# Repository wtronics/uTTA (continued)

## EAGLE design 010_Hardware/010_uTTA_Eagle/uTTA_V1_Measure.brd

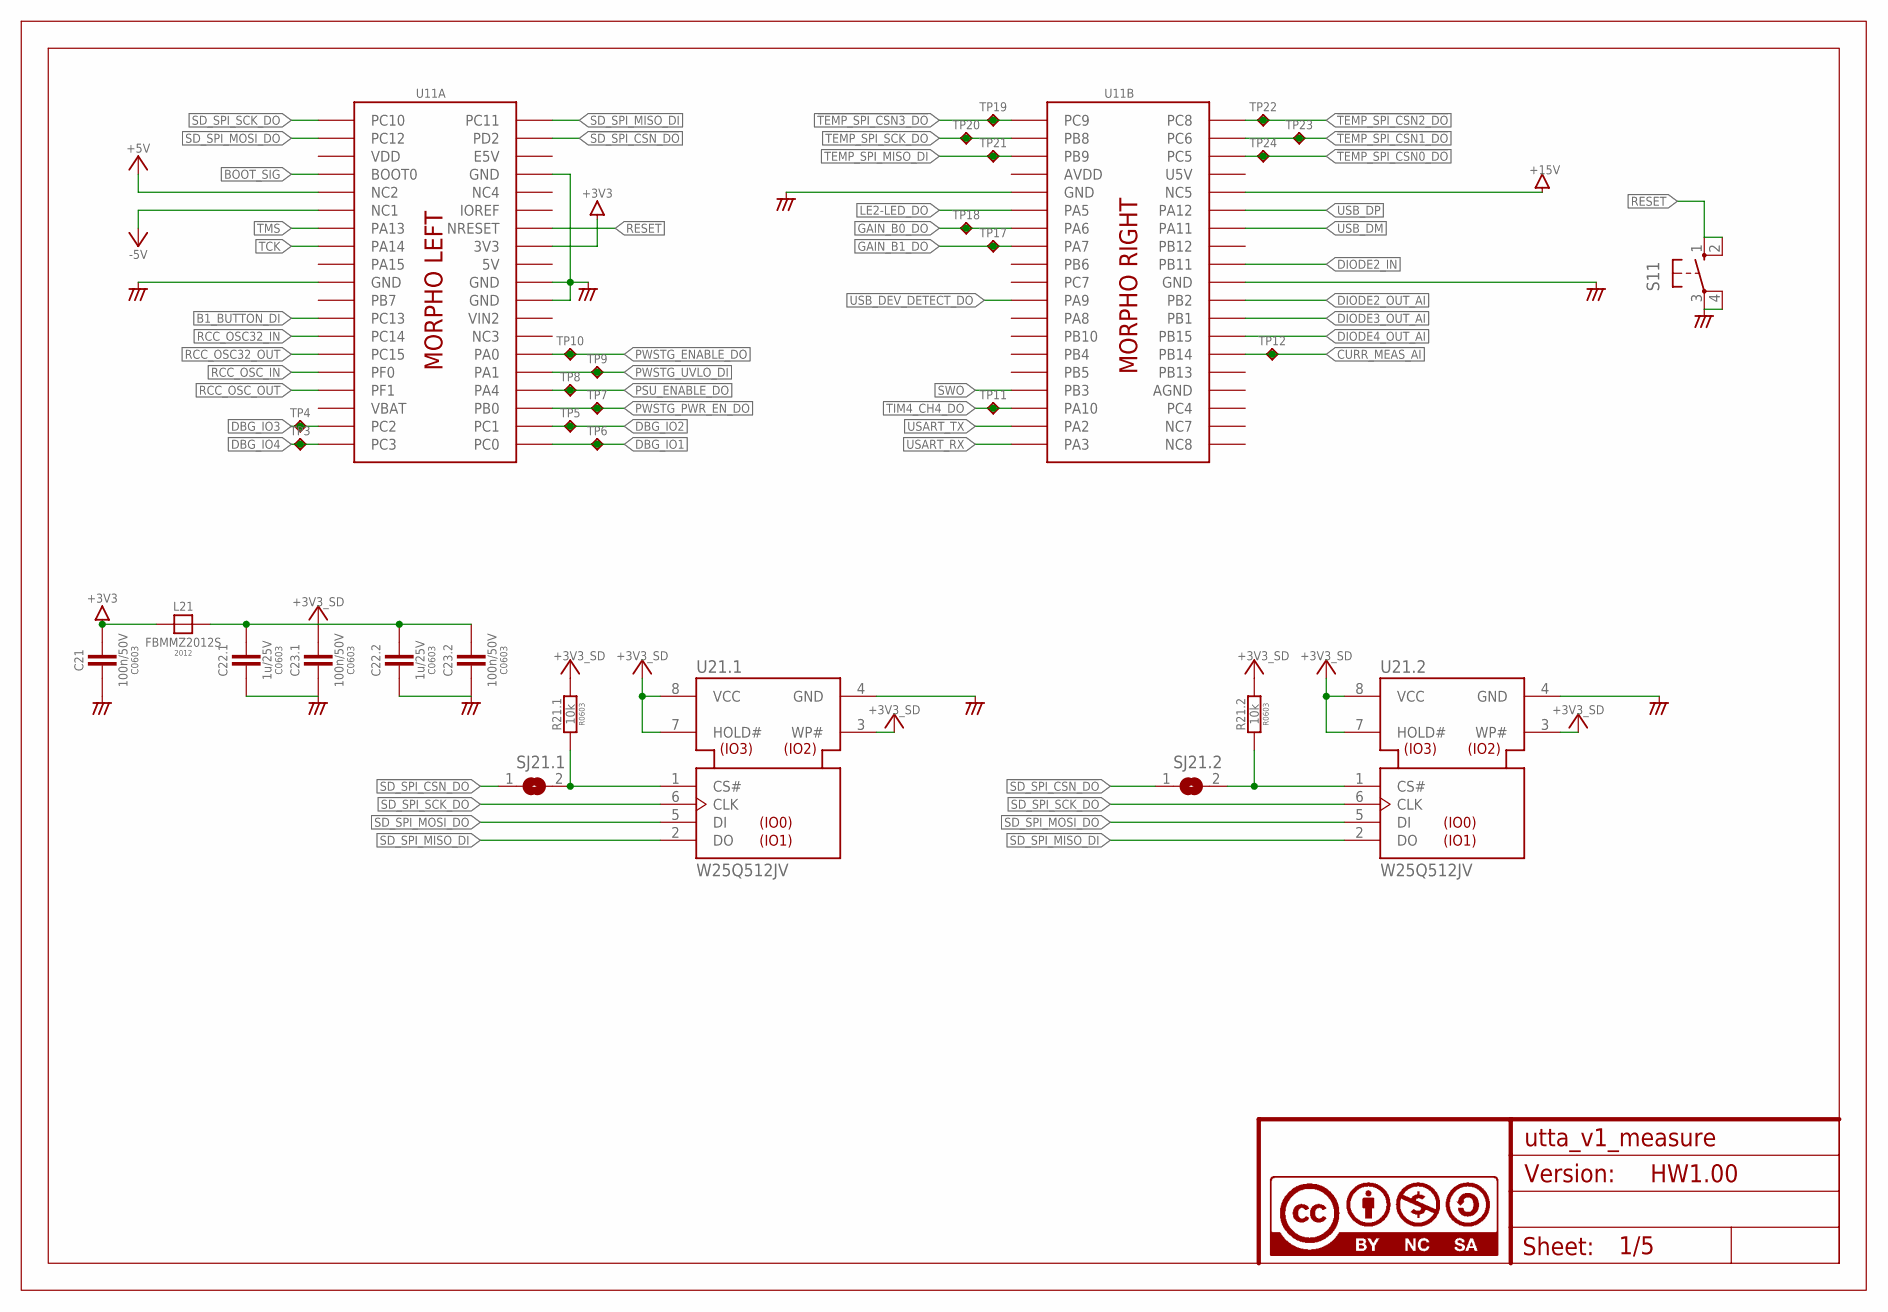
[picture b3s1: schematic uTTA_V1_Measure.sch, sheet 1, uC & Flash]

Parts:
C21, C23.1, C23.2: 100n/50V; C0603
C22.1, C22.2: 1u/25V; C0603
L21: FBMMZ2012S; FB2012
R21.1, R21.2: 10k; R0603
S11: 10-XX; B3F-10XX
SJ21.1, SJ21.2: SJ
TP3, TP4, TP5, TP6, TP7, TP8, TP9, TP10, TP11, TP12, TP17, TP18, TP19, TP20, TP21, TP22, TP23, TP24: TPC90H30; C90H30
U11: NUCLEO_F103_BOT; NUCLEO_BRD64_LOWER
U21.1, U21.2: W25Q512JV; SO08W
U$3: A4L-LOC_CC_BY_NC_SA; A4_LOC_CC_BY_NC_SA

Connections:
5V: U11.L_5V (5V)
!SD_SPI_CSN_DO: SJ21.1.1, SJ21.2.1, U11.L_PD2 (PD2)
!TEMP_SPI_CSN0_DO: TP24.P$1, U11.R_PC5 (PC5); also elsewhere on the board
!TEMP_SPI_CSN1_DO: TP23.P$1, U11.R_PC6 (PC6); also elsewhere on the board
!TEMP_SPI_CSN2_DO: TP22.P$1, U11.R_PC8 (PC8); also elsewhere on the board
!TEMP_SPI_CSN3_DO: TP19.P$1, U11.R_PC9 (PC9); also elsewhere on the board
+3V3: C21.1, L21.1, U11.L_3V3 (3V3); also elsewhere on the board
+5V: U11.L_NC2 (NC2); also elsewhere on the board
+5V/4: C22.1.1, C22.2.1, C23.1.1, C23.2.1, L21.2, R21.1.1, R21.2.1, U21.1.3 (WP#), U21.1.7 (HOLD#), U21.1.8 (VCC), U21.2.3 (WP#), U21.2.7 (HOLD#), U21.2.8 (VCC)
+15V: U11.R_NC5 (NC5)
-5V: U11.L_NC1 (NC1); also elsewhere on the board
AGND: C21.2, C22.1.2, C22.2.2, C23.1.2, C23.2.2, S11.3, S11.4 (P1), U11.L_GND (GND), U11.L_GND3 (GND), U11.L_GND4 (GND), U11.L_GND5 (GND), U11.R_AGND (AGND), U11.R_GND7 (GND), U11.R_GND8 (GND), U21.1.4 (GND), U21.2.4 (GND); also elsewhere on the board
AVDD: U11.R_AVDD (AVDD)
B1_BUTTON_DI: U11.L_PC13 (PC13)
BOOT_SIG: U11.L_BOOT0 (BOOT0)
CURR_MEAS_AI: TP12.P$1, U11.R_PB14 (PB14)
DBG_IO1: TP6.P$1, U11.L_PC0 (PC0)
DBG_IO2: TP5.P$1, U11.L_PC1 (PC1)
DBG_IO3: TP4.P$1, U11.L_PC2 (PC2)
DBG_IO4: TP3.P$1, U11.L_PC3 (PC3)
DIODE2_IN: U11.R_PB11 (PB11); also elsewhere on the board
DIODE2_OUT_AI: U11.R_PB2 (PB2); also elsewhere on the board
DIODE3_OUT_AI: U11.R_PB1 (PB1); also elsewhere on the board
DIODE4_OUT_AI: U11.R_PB15 (PB15); also elsewhere on the board
E5V: U11.L_E5V (E5V)
GAIN_B0_DO: TP18.P$1, U11.R_PA6 (PA6); also elsewhere on the board
GAIN_B1_DO: TP17.P$1, U11.R_PA7 (PA7); also elsewhere on the board
LE2-LED_DO: U11.R_PA5 (PA5)
unnamed: R21.1.2, SJ21.1.2, U21.1.1 (CS#)
unnamed: R21.2.2, SJ21.2.2, U21.2.1 (CS#)
PSU_ENABLE_DO: TP8.P$1, U11.L_PA4 (PA4)
PWSTG_ENABLE_DO: TP10.P$1, U11.L_PA0 (PA0)
PWSTG_PWR_EN_DO: TP7.P$1, U11.L_PB0 (PB0)
PWSTG_UVLO_DI: TP9.P$1, U11.L_PA1 (PA1)
RCC_OSC32_IN: U11.L_PC14 (PC14)
RCC_OSC32_OUT: U11.L_PC15 (PC15)
RCC_OSC_IN: U11.L_PF0 (PF0)
RCC_OSC_OUT: U11.L_PF1 (PF1)
RESET: S11.1 (S), S11.2 (S1), U11.L_RESET (NRESET)
SD_SPI_MISO_DI: U11.L_PC11 (PC11), U21.1.2 (DO), U21.2.2 (DO)
SD_SPI_MOSI_DO: U11.L_PC12 (PC12), U21.1.5 (DI), U21.2.5 (DI); also elsewhere on the board
SD_SPI_SCK_DO: U11.L_PC10 (PC10), U21.1.6 (CLK), U21.2.6 (CLK); also elsewhere on the board
SWO: U11.R_PB3 (PB3)
TCK: U11.L_PA14 (PA14)
TEMP_SPI_MISO_DI: TP21.P$1, U11.R_PB9 (PB9); also elsewhere on the board
TEMP_SPI_SCK_DO: TP20.P$1, U11.R_PB8 (PB8); also elsewhere on the board
TIM4_CH4_DO: TP11.P$1, U11.R_PA10 (PA10)
TMS: U11.L_PA13 (PA13)
U5V: U11.R_U5V (U5V)
USART_RX: U11.R_PA3 (PA3)
USART_TX: U11.R_PA2 (PA2)
USB_DEV_DETECT_DO: U11.R_PA9 (PA9)
USB_DM: U11.R_PA11 (PA11)
USB_DP: U11.R_PA12 (PA12)
VBAT: U11.L_VBAT (VBAT)
VDD: U11.L_VDD (VDD)
VIN2: U11.L_VIN (VIN2)

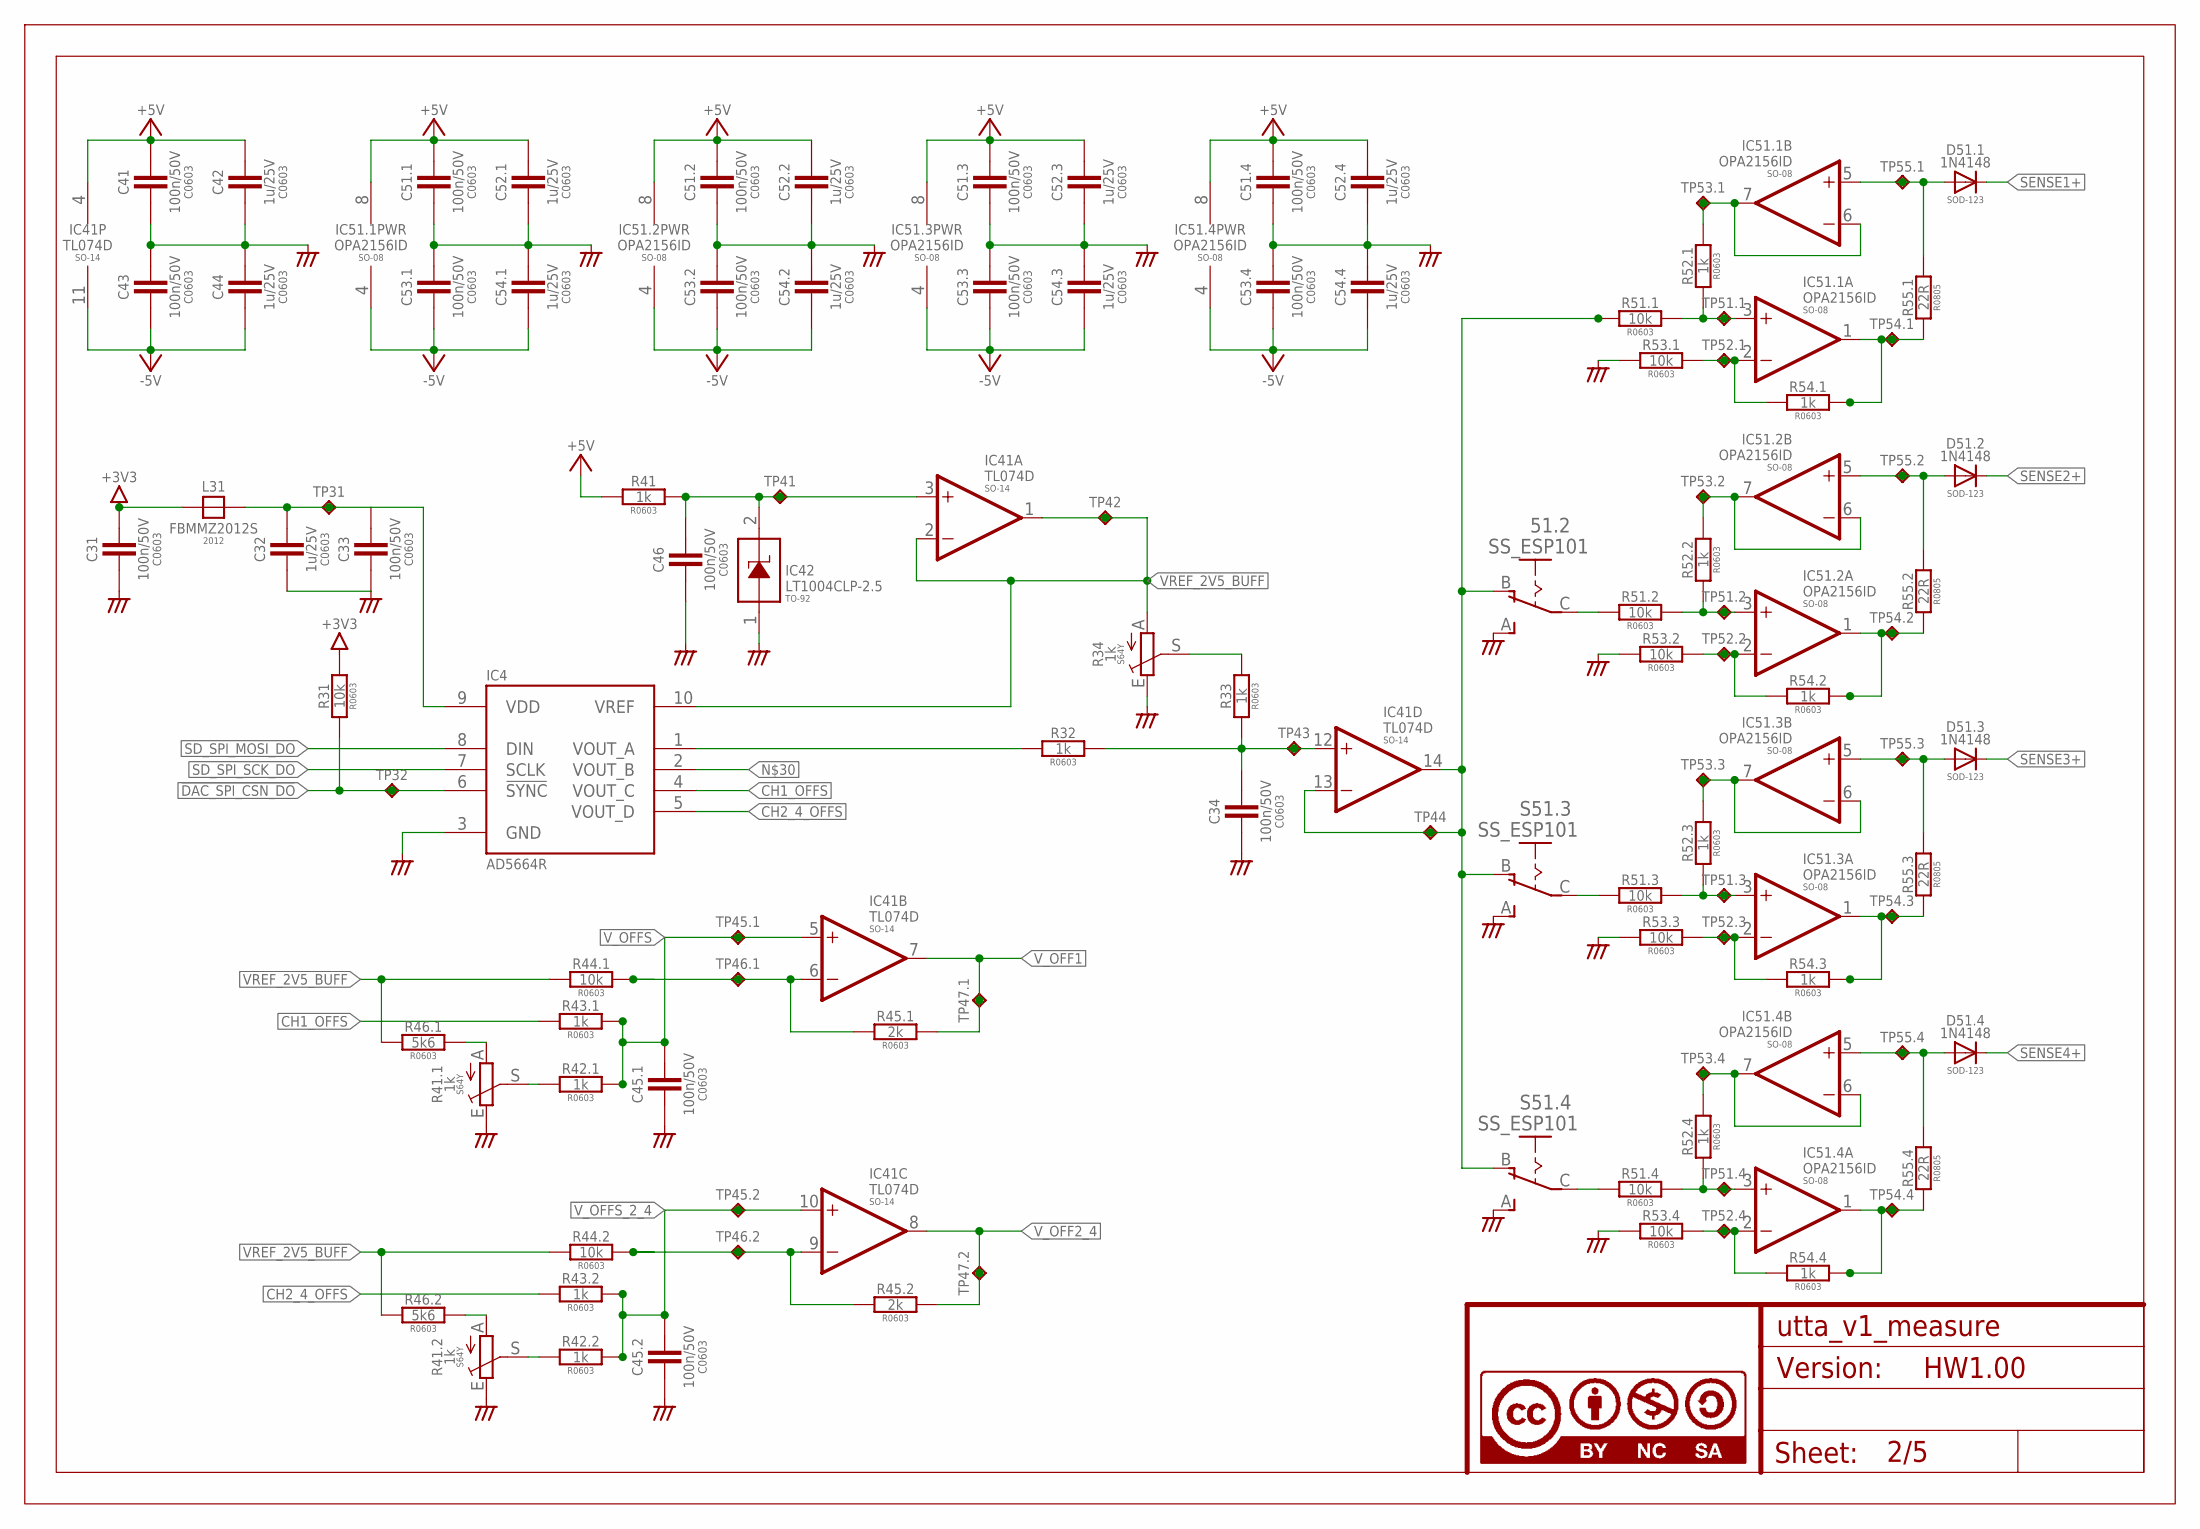
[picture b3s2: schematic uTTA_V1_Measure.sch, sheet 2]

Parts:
51.2: SS_ESP101
C31, C33, C34, C41, C43, C45.1, C45.2, C46, C51.1, C51.2, C51.3, C51.4, C53.1, C53.2, C53.3, C53.4: 100n/50V; C0603
C32, C42, C44, C52.1, C52.2, C52.3, C52.4, C54.1, C54.2, C54.3, C54.4: 1u/25V; C0603
D51.1, D51.2, D51.3, D51.4: 1N4148; SOD123
IC4: AD5664R; MSOP10
IC41: TL074D; SO14
IC42: LT1004CLP-2.5; TO92-
IC51.1, IC51.2, IC51.3, IC51.4: OPA2156ID; SO08
L31: FBMMZ2012S; FB2012
R31, R44.1, R44.2, R51.1, R51.2, R51.3, R51.4, R53.1, R53.2, R53.3, R53.4: 10k; R0603
R32, R33, R41, R42.1, R42.2, R43.1, R43.2, R52.1, R52.2, R52.3, R52.4, R54.1, R54.2, R54.3, R54.4: 1k; R0603
R34, R41.1, R41.2: 1k; S64Y
R45.1, R45.2: 2k; R0603
R46.1, R46.2: 5k6; R0603
R55.1, R55.2, R55.3, R55.4: 22R; R0805
S51.3, S51.4: SS_ESP101
TP31, TP32, TP41, TP42, TP43, TP44, TP45.1, TP45.2, TP46.1, TP46.2, TP47.1, TP47.2, TP51.1, TP51.2, TP51.3, TP51.4, TP52.1, TP52.2, TP52.3, TP52.4, TP53.1, TP53.2, TP53.3, TP53.4, TP54.1, TP54.2, TP54.3, TP54.4, TP55.1, TP55.2, TP55.3, TP55.4: TP; C90
U$10: A4L-LOC_CC_BY_NC_SA; A4_LOC_CC_BY_NC_SA

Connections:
!DAC_SPI_CSN_DO: IC4.6 (!SYNC), R31.2, TP32.P$1
+3V3: C31.1, L31.1, R31.1; also elsewhere on the board
+5V: C41.1, C42.1, C51.1.1, C51.2.1, C51.3.1, C51.4.1, C52.1.1, C52.2.1, C52.3.1, C52.4.1, IC41.4 (V+), IC51.1.8 (V+), IC51.2.8 (V+), IC51.3.8 (V+), IC51.4.8 (V+), R41.1; also elsewhere on the board
-5V: C43.2, C44.2, C53.1.2, C53.2.2, C53.3.2, C53.4.2, C54.1.2, C54.2.2, C54.3.2, C54.4.2, IC41.11 (V-), IC51.1.4 (V-), IC51.2.4 (V-), IC51.3.4 (V-), IC51.4.4 (V-); also elsewhere on the board
AGND: 51.2.A (S), C31.2, C32.2, C33.2, C34.2, C41.2, C42.2, C43.1, C44.1, C45.1.2, C45.2.2, C46.2, C51.1.2, C51.2.2, C51.3.2, C51.4.2, C52.1.2, C52.2.2, C52.3.2, C52.4.2, C53.1.1, C53.2.1, C53.3.1, C53.4.1, C54.1.1, C54.2.1, C54.3.1, C54.4.1, IC4.3 (GND), IC42.1 (A), R34.E, R41.1.E, R41.2.E, R53.1.1, R53.2.1, R53.3.1, R53.4.1, S51.3.A (S), S51.4.A (S); also elsewhere on the board
CH1_OFFS: IC4.4 (VOUT_C), R43.1.1
CH2_4_OFFS: IC4.5 (VOUT_D), R43.2.1
unnamed: C32.1, C33.1, IC4.9 (VDD), L31.2, TP31.P$1
unnamed: IC51.1.6 (-IN), IC51.1.7 (OUT), R52.1.2, TP53.1.P$1
unnamed: IC51.2.6 (-IN), IC51.2.7 (OUT), R52.2.2, TP53.2.P$1
unnamed: D51.2.A, IC51.2.5 (+IN), R55.2.2, TP55.2.P$1
unnamed: IC51.2.1 (OUT), R54.2.2, R55.2.1, TP54.2.P$1
unnamed: D51.1.A, IC51.1.5 (+IN), R55.1.2, TP55.1.P$1
unnamed: IC51.1.1 (OUT), R54.1.2, R55.1.1, TP54.1.P$1
unnamed: IC51.1.3 (+IN), R51.1.2, R52.1.1, TP51.1.P$1
unnamed: IC51.1.2 (-IN), R53.1.2, R54.1.1, TP52.1.P$1
unnamed: IC51.2.3 (+IN), R51.2.2, R52.2.1, TP51.2.P$1
unnamed: IC51.2.2 (-IN), R53.2.2, R54.2.1, TP52.2.P$1
unnamed: IC51.3.6 (-IN), IC51.3.7 (OUT), R52.3.2, TP53.3.P$1
unnamed: D51.3.A, IC51.3.5 (+IN), R55.3.2, TP55.3.P$1
unnamed: IC51.3.1 (OUT), R54.3.2, R55.3.1, TP54.3.P$1
unnamed: IC51.3.3 (+IN), R51.3.2, R52.3.1, TP51.3.P$1
unnamed: IC51.3.2 (-IN), R53.3.2, R54.3.1, TP52.3.P$1
unnamed: IC51.4.6 (-IN), IC51.4.7 (OUT), R52.4.2, TP53.4.P$1
unnamed: D51.4.A, IC51.4.5 (+IN), R55.4.2, TP55.4.P$1
unnamed: IC51.4.1 (OUT), R54.4.2, R55.4.1, TP54.4.P$1
unnamed: IC51.4.3 (+IN), R51.4.2, R52.4.1, TP51.4.P$1
unnamed: IC51.4.2 (-IN), R53.4.2, R54.4.1, TP52.4.P$1
unnamed: 51.2.C, R51.2.1
unnamed: R51.3.1, S51.3.C
unnamed: R51.4.1, S51.4.C
unnamed: 51.2.B (O), IC41.13 (-IN), IC41.14 (OUT), R51.1.1, S51.3.B (O), S51.4.B (O), TP44.P$1
unnamed: IC4.1 (VOUT_A), R32.1
unnamed: C34.1, IC41.12 (+IN), R32.2, R33.2, TP43.P$1
unnamed: R33.1, R34.S
SD_SPI_MOSI_DO: IC4.8 (DIN); also elsewhere on the board
SD_SPI_SCK_DO: IC4.7 (SCLK); also elsewhere on the board
SENSE1+: D51.1.C; also elsewhere on the board
SENSE2+: D51.2.C; also elsewhere on the board
SENSE3+: D51.3.C; also elsewhere on the board
SENSE4+: D51.4.C; also elsewhere on the board
VOFFS_RR: IC41.6 (-IN), R44.1.1, R45.1.2, TP46.1.P$1
VOFFS_RR1: IC41.9 (-IN), R44.2.1, R45.2.2, TP46.2.P$1
VREF: C46.1, IC41.3 (+IN), IC42.2 (C), R41.2, TP41.P$1
VREF_2V5_BUFF: IC4.10 (VREF), IC41.1 (OUT), IC41.2 (-IN), R34.A, R44.1.2, R44.2.2, R46.1.2, R46.2.2, TP42.P$1
VREF_RR1: R41.1.A, R46.1.1
VREF_RR2: R41.2.A, R46.2.1
VREF_TRIM: R41.1.S, R42.1.1
VREF_TRIM1: R41.2.S, R42.2.1
V_OFF1: IC41.7 (OUT), R45.1.1, TP47.1.P$1; also elsewhere on the board
V_OFF2_4: IC41.8 (OUT), R45.2.1, TP47.2.P$1; also elsewhere on the board
V_OFFS: C45.1.1, IC41.5 (+IN), R42.1.2, R43.1.2, TP45.1.P$1
V_OFFS_2_4: C45.2.1, IC41.10 (+IN), R42.2.2, R43.2.2, TP45.2.P$1

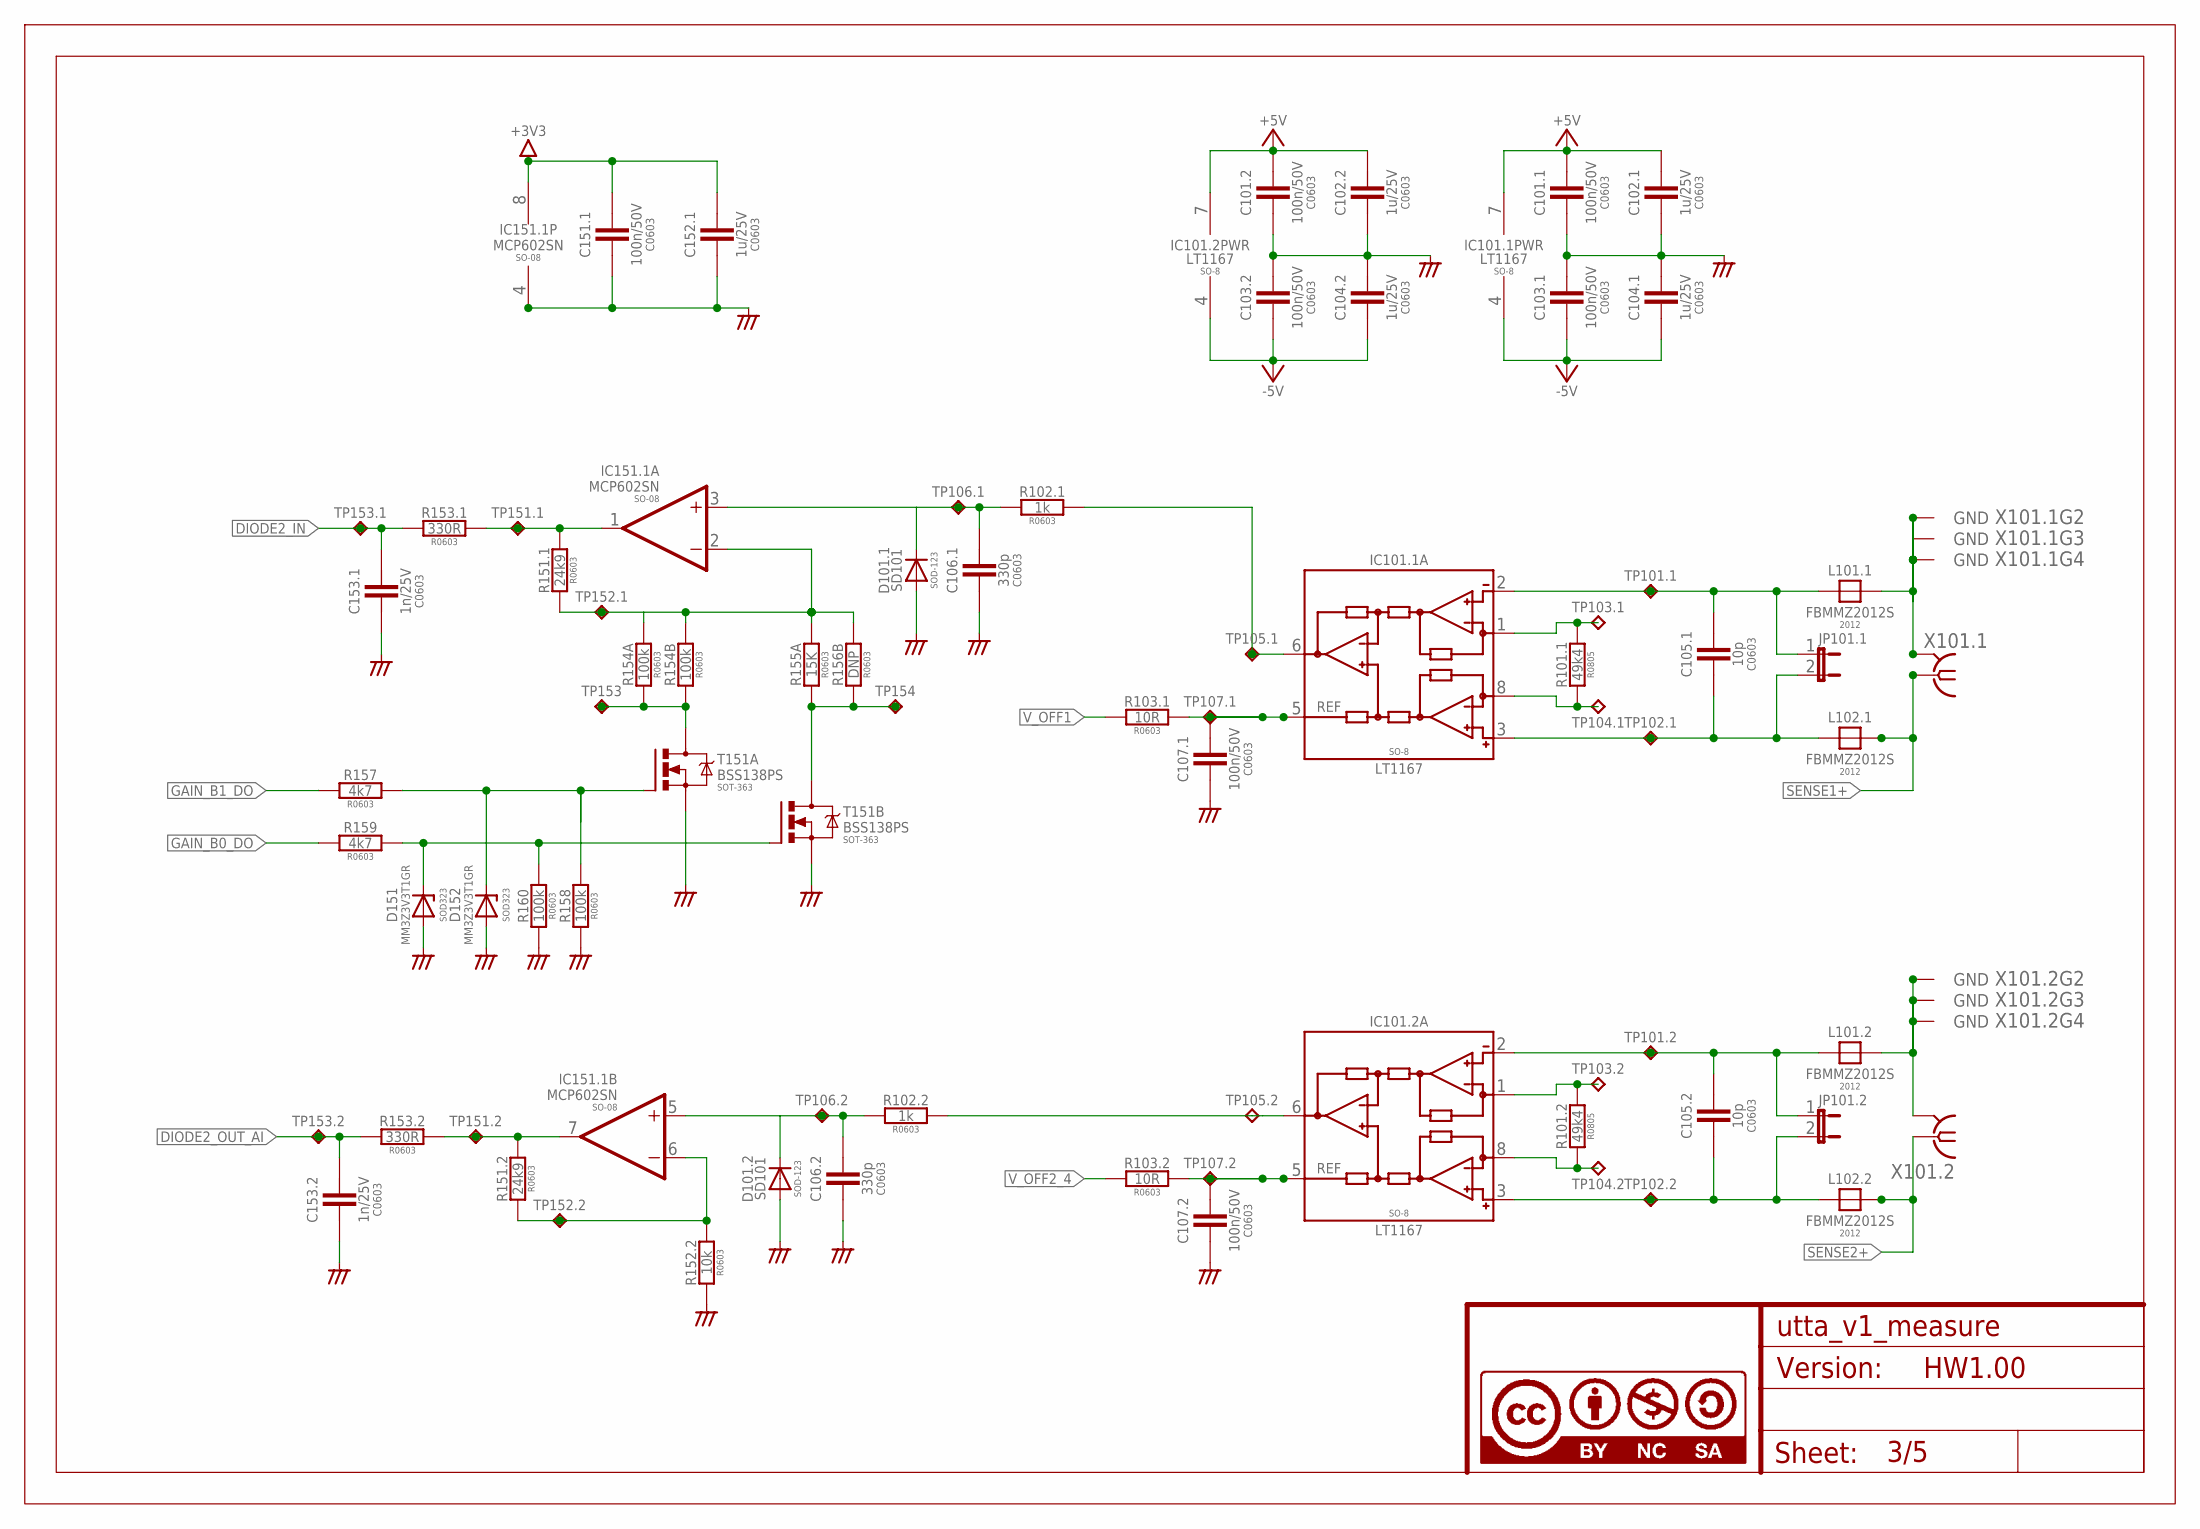
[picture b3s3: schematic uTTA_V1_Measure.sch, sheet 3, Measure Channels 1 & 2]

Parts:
C101.1, C101.2, C103.1, C103.2, C107.1, C107.2, C151.1: 100n/50V; C0603
C102.1, C102.2, C104.1, C104.2, C152.1: 1u/25V; C0603
C105.1, C105.2: 10p; C0603
C106.1, C106.2: 330p; C0603
C153.1, C153.2: 1n/25V; C0603
D101.1, D101.2: SD101; SOD123
D151, D152: MM3Z3V3T1GR; SOD323-R
IC101.1, IC101.2: LT1167; SO08
IC151.1: MCP602SN; SO08
JP101.1, JP101.2: JP1E; JP1
L101.1, L101.2, L102.1, L102.2: FBMMZ2012S; FB2012
R101.1, R101.2: 49k4; R0805
R102.1, R102.2: 1k; R0603
R103.1, R103.2: 10R; R0603
R151.1, R151.2: 24k9; R0603
R152.2: 10k; R0603
R153.1, R153.2: 330R; R0603
R154A, R154B, R158, R160: 100k; R0603
R155A: 15K; R0603
R156B: DNP; R0603
R157, R159: 4k7; R0603
T151: BSS138PS; SOT363_PHILIPS
TP101.1, TP101.2, TP102.1, TP102.2, TP103.1, TP103.2, TP104.1, TP104.2, TP105.1, TP105.2, TP107.1, TP107.2, TP151.1, TP151.2, TP152.1, TP152.2, TP153, TP154: TP; C90
TP106.1, TP106.2, TP153.1, TP153.2: TPC90H30; C90H30
U$2: A4L-LOC_CC_BY_NC_SA; A4_LOC_CC_BY_NC_SA
X101.1, X101.2: BU-SMA-GSPECIAL; BU_SMA_3P

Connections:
+3V3: C151.1.1, C152.1.1, IC151.1.8 (V+); also elsewhere on the board
+5V: C101.1.1, C101.2.1, C102.1.1, C102.2.1, IC101.1.7 (V+), IC101.2.7 (V+); also elsewhere on the board
-5V: C103.1.2, C103.2.2, C104.1.2, C104.2.2, IC101.1.4 (V-), IC101.2.4 (V-); also elsewhere on the board
AGND: C101.1.2, C101.2.2, C102.1.2, C102.2.2, C103.1.1, C103.2.1, C104.1.1, C104.2.1, C106.1.2, C106.2.2, C107.1.2, C107.2.2, C151.1.2, C152.1.2, C153.1.2, C153.2.2, D101.1.A, D101.2.A, D151.A, D152.A, IC151.1.4 (V-), R152.2.1, R158.1, R160.1, T151.1 (S), T151.4 (S); also elsewhere on the board
AMP1_OUT: IC151.1.1 (OUT), R151.1.2, R153.1.2, TP151.1.P$1
AMP1_RG_B0: R155A.1, R156B.1, T151.6 (D), TP154.P$1
AMP1_RG_B1: R154A.1, R154B.1, T151.3 (D), TP153.P$1
AMP2_FB: IC151.1.6 (-IN), R151.2.1, R152.2.2, TP152.2.P$1
AMP2_OUT: IC151.1.7 (OUT), R151.2.2, R153.2.2, TP151.2.P$1
B0_GATE: D151.C, R159.2, R160.2, T151.5 (G)
B1_GATE: D152.C, R157.2, R158.2, T151.2 (G)
DIFF_AMP1_OUT: IC101.1.6 (OUT), R102.1.2, TP105.1.P$1
DIFF_AMP2_OUT: IC101.2.6 (OUT), R102.2.2, TP105.2.P$1
DIODE2_IN: C106.2.1, C153.1.1, D101.2.C, IC151.1.5 (+IN), R102.2.1, R153.1.1, TP106.2.P$1, TP153.1.P$1; also elsewhere on the board
DIODE2_OUT_AI: C153.2.1, R153.2.1, TP153.2.P$1; also elsewhere on the board
GAIN1+: IC101.1.8 (RG), R101.1.2, TP104.1.P$1
GAIN1-: IC101.1.1 (RG), R101.1.1, TP103.1.P$1
GAIN2+: IC101.2.8 (RG), R101.2.2, TP104.2.P$1
GAIN2-: IC101.2.1 (RG), R101.2.1, TP103.2.P$1
GAIN_B0_DO: R159.1; also elsewhere on the board
GAIN_B1_DO: R157.1; also elsewhere on the board
IN1+: C105.1.2, IC101.1.3 (+IN), JP101.1.2, L102.1.1, TP102.1.P$1
IN1-: C105.1.1, IC101.1.2 (-IN), JP101.1.1, L101.1.1, TP101.1.P$1
IN2+: C105.2.2, IC101.2.3 (+IN), JP101.2.2, L102.2.1, TP102.2.P$1
IN2-: C105.2.1, IC101.2.2 (-IN), JP101.2.1, L101.2.1, TP101.2.P$1
PGA_DIODE1_IN: C106.1.1, D101.1.C, IC151.1.3 (+IN), R102.1.1, TP106.1.P$1
SENSE1+: L102.1.2, X101.1.C1 (1), X101.1.C2 (1); also elsewhere on the board
SENSE1-: L101.1.2, X101.1.@GND1 (GND), X101.1.@GND2 (GND), X101.1.@GND3 (GND), X101.1.@GND4 (GND), X101.1.GND
SENSE2+: L102.2.2, X101.2.C1 (1), X101.2.C2 (1); also elsewhere on the board
SENSE2-: L101.2.2, X101.2.@GND1 (GND), X101.2.@GND2 (GND), X101.2.@GND3 (GND), X101.2.@GND4 (GND), X101.2.GND
TP152.1: IC151.1.2 (-IN), R151.1.1, R154A.2, R154B.2, R155A.2, R156B.2, TP152.1.P$1
V_OFF1: R103.1.1; also elsewhere on the board
V_OFF2_4: R103.2.1; also elsewhere on the board
V_OPREF1: C107.1.1, IC101.1.5 (REF), R103.1.2, TP107.1.P$1
V_OPREF2: C107.2.1, IC101.2.5 (REF), R103.2.2, TP107.2.P$1

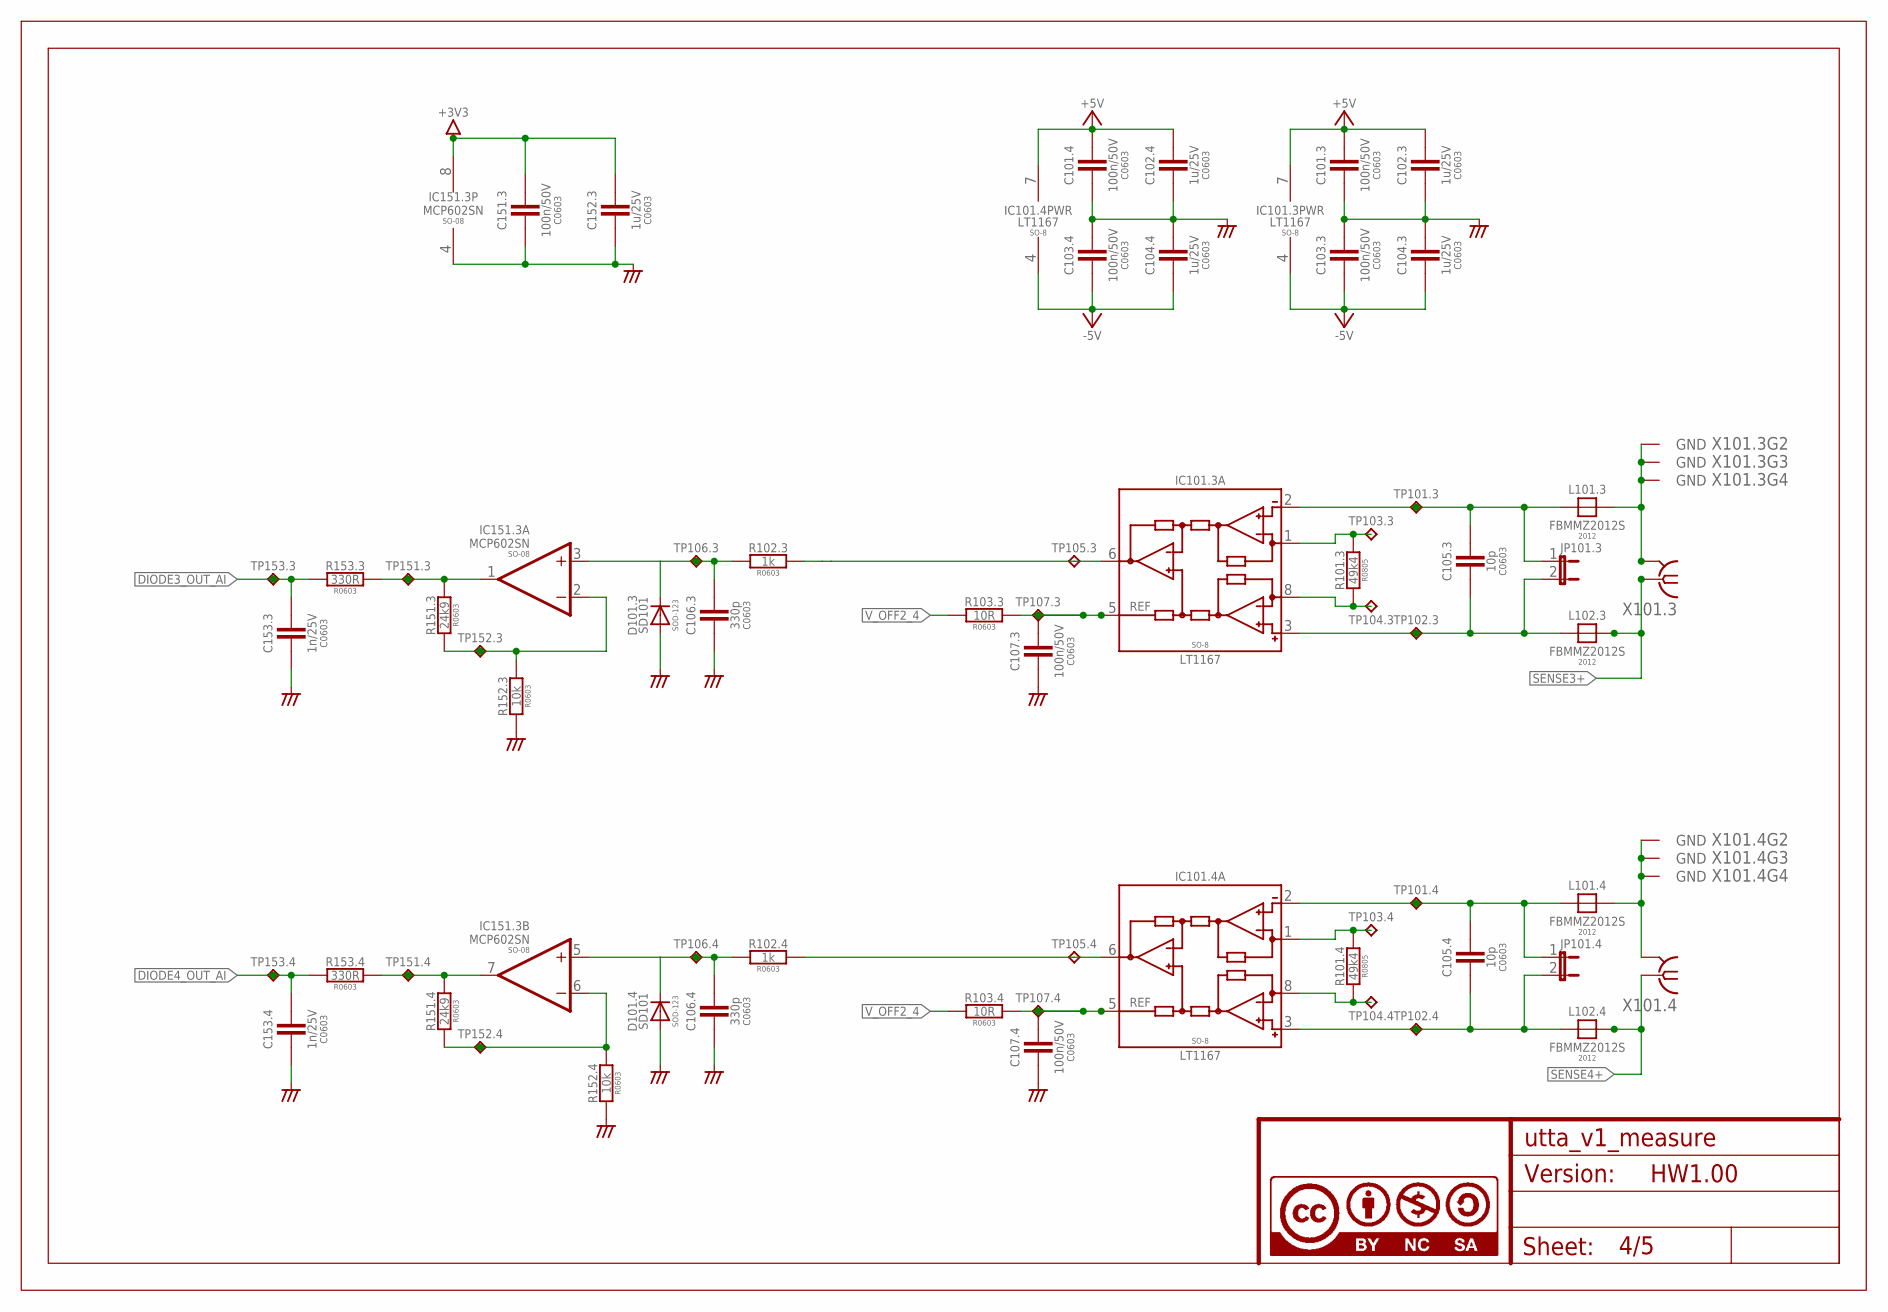
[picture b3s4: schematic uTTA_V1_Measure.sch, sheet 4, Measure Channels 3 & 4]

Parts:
C101.3, C101.4, C103.3, C103.4, C107.3, C107.4, C151.3: 100n/50V; C0603
C102.3, C102.4, C104.3, C104.4, C152.3: 1u/25V; C0603
C105.3, C105.4: 10p; C0603
C106.3, C106.4: 330p; C0603
C153.3, C153.4: 1n/25V; C0603
D101.3, D101.4: SD101; SOD123
IC101.3, IC101.4: LT1167; SO08
IC151.3: MCP602SN; SO08
JP101.3, JP101.4: JP1E; JP1
L101.3, L101.4, L102.3, L102.4: FBMMZ2012S; FB2012
R101.3, R101.4: 49k4; R0805
R102.3, R102.4: 1k; R0603
R103.3, R103.4: 10R; R0603
R151.3, R151.4: 24k9; R0603
R152.3, R152.4: 10k; R0603
R153.3, R153.4: 330R; R0603
TP101.3, TP101.4, TP102.3, TP102.4, TP103.3, TP103.4, TP104.3, TP104.4, TP105.3, TP105.4, TP107.3, TP107.4, TP151.3: TP; C90
TP106.3, TP106.4, TP151.4, TP152.3, TP152.4, TP153.3, TP153.4: TPC90H30; C90H30
U$4: A4L-LOC_CC_BY_NC_SA; A4_LOC_CC_BY_NC_SA
X101.3, X101.4: BU-SMA-GSPECIAL; BU_SMA_3P

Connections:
+3V3: C151.3.1, C152.3.1, IC151.3.8 (V+); also elsewhere on the board
+5V: C101.3.1, C101.4.1, C102.3.1, C102.4.1, IC101.3.7 (V+), IC101.4.7 (V+); also elsewhere on the board
-5V: C103.3.2, C103.4.2, C104.3.2, C104.4.2, IC101.3.4 (V-), IC101.4.4 (V-); also elsewhere on the board
AGND: C101.3.2, C101.4.2, C102.3.2, C102.4.2, C103.3.1, C103.4.1, C104.3.1, C104.4.1, C106.3.2, C106.4.2, C107.3.2, C107.4.2, C151.3.2, C152.3.2, C153.3.2, C153.4.2, D101.3.A, D101.4.A, IC151.3.4 (V-), R152.3.1, R152.4.1; also elsewhere on the board
AMP3_FB: IC151.3.2 (-IN), R151.3.1, R152.3.2, TP152.3.P$1
AMP3_OUT: IC151.3.1 (OUT), R151.3.2, R153.3.2, TP151.3.P$1
AMP4_FB: IC151.3.6 (-IN), R151.4.1, R152.4.2, TP152.4.P$1
AMP4_OUT: IC151.3.7 (OUT), R151.4.2, R153.4.2, TP151.4.P$1
DIFF_AMP3_OUT: IC101.3.6 (OUT), R102.3.2, TP105.3.P$1
DIFF_AMP4_OUT: IC101.4.6 (OUT), R102.4.2, TP105.4.P$1
DIODE3_IN: C106.3.1, D101.3.C, IC151.3.3 (+IN), R102.3.1, TP106.3.P$1
DIODE3_OUT_AI: C153.3.1, R153.3.1, TP153.3.P$1; also elsewhere on the board
DIODE4_IN: C106.4.1, D101.4.C, IC151.3.5 (+IN), R102.4.1, TP106.4.P$1
DIODE4_OUT_AI: C153.4.1, R153.4.1, TP153.4.P$1; also elsewhere on the board
GAIN3+: IC101.3.8 (RG), R101.3.2, TP104.3.P$1
GAIN3-: IC101.3.1 (RG), R101.3.1, TP103.3.P$1
GAIN4+: IC101.4.8 (RG), R101.4.2, TP104.4.P$1
GAIN4-: IC101.4.1 (RG), R101.4.1, TP103.4.P$1
IN3+: C105.3.2, IC101.3.3 (+IN), JP101.3.2, L102.3.1, TP102.3.P$1
IN3-: C105.3.1, IC101.3.2 (-IN), JP101.3.1, L101.3.1, TP101.3.P$1
IN4+: C105.4.2, IC101.4.3 (+IN), JP101.4.2, L102.4.1, TP102.4.P$1
IN4-: C105.4.1, IC101.4.2 (-IN), JP101.4.1, L101.4.1, TP101.4.P$1
SENSE3+: L102.3.2, X101.3.C1 (1), X101.3.C2 (1); also elsewhere on the board
SENSE3-: L101.3.2, X101.3.@GND1 (GND), X101.3.@GND2 (GND), X101.3.@GND3 (GND), X101.3.@GND4 (GND), X101.3.GND
SENSE4+: L102.4.2, X101.4.C1 (1), X101.4.C2 (1); also elsewhere on the board
SENSE4-: L101.4.2, X101.4.@GND1 (GND), X101.4.@GND2 (GND), X101.4.@GND3 (GND), X101.4.@GND4 (GND), X101.4.GND
V_OFF2_4: R103.3.1, R103.4.1; also elsewhere on the board
V_OPREF3: C107.3.1, IC101.3.5 (REF), R103.3.2, TP107.3.P$1
V_OPREF4: C107.4.1, IC101.4.5 (REF), R103.4.2, TP107.4.P$1
